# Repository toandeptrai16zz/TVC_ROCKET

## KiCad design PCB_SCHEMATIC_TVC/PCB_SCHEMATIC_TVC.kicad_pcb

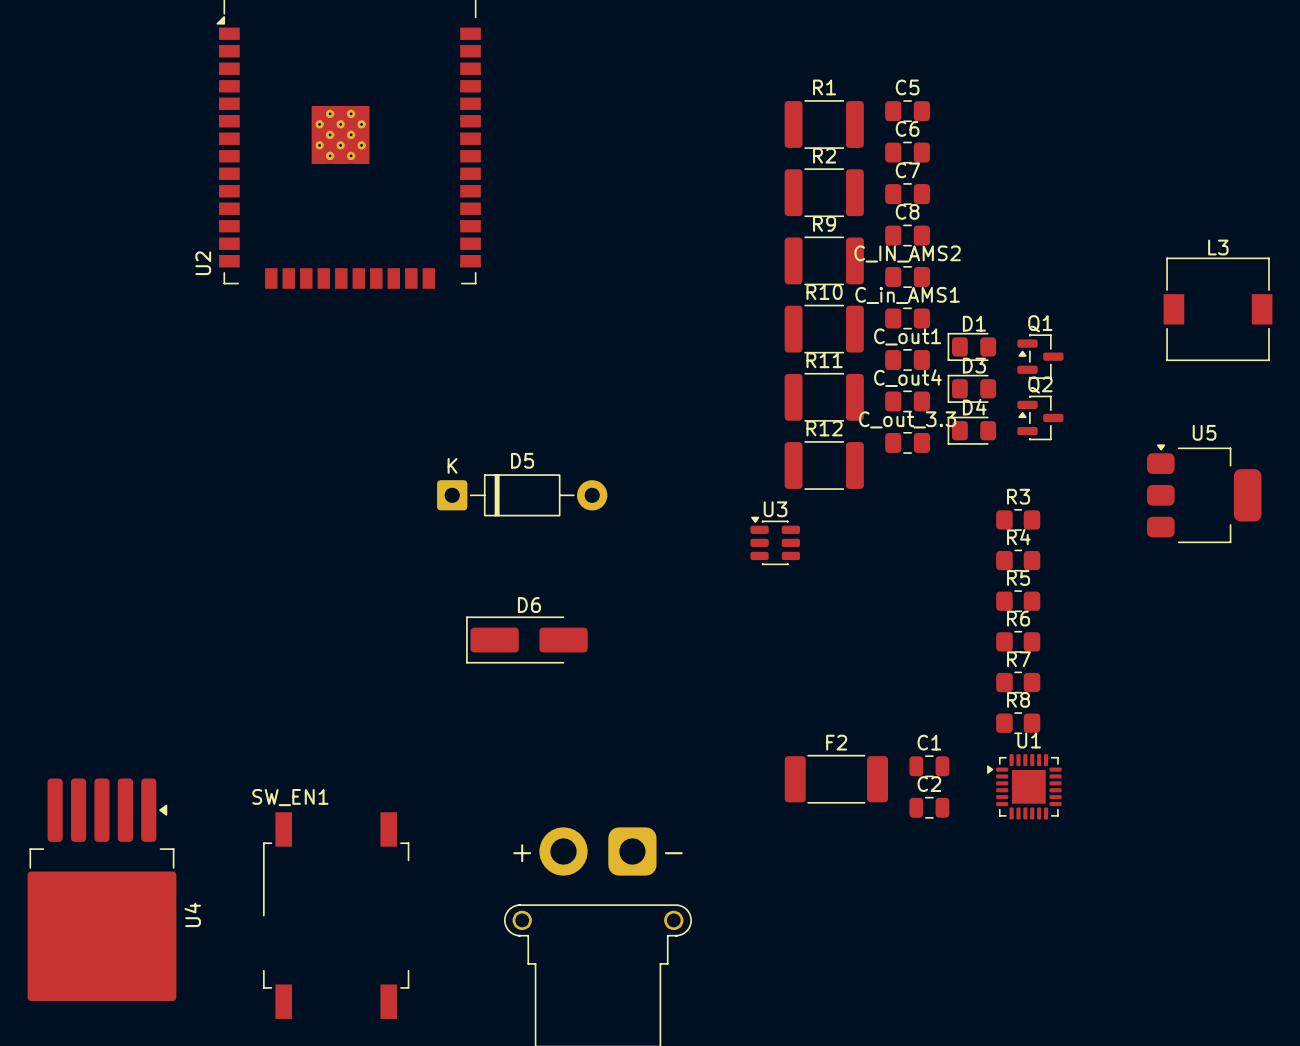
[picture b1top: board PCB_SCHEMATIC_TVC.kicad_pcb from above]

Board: 2 copper layers, 39 parts (0 on the bottom side), 21 nets, no tracks yet.

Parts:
C1, C2: 10uF; C_0805_2012Metric
C5: 4.7uF; C_0805_2012Metric_Pad1.18x1.45mm_HandSolder
C6, C8: 100nF; C_0805_2012Metric_Pad1.18x1.45mm_HandSolder
C7: 10uF; C_0805_2012Metric_Pad1.18x1.45mm_HandSolder
C_IN_AMS2: 1uF; C_0805_2012Metric_Pad1.18x1.45mm_HandSolder
C_in_AMS1: 10uF; C_0805_2012Metric_Pad1.18x1.45mm_HandSolder
C_out1: 220uF; C_0805_2012Metric_Pad1.18x1.45mm_HandSolder
C_out4: 1uF; C_0805_2012Metric_Pad1.18x1.45mm_HandSolder
C_out_3.3: 10uF; C_0805_2012Metric_Pad1.18x1.45mm_HandSolder
D1, D3, D4: LED; LED_0805_2012Metric_Pad1.15x1.40mm_HandSolder
D5: 1N5817; D_DO-41_SOD81_P10.16mm_Horizontal
D6: SS34; D_SMA_Handsoldering
F2: Fuse; Fuse_2512_6332Metric_Pad1.52x3.35mm_HandSolder
J2: Conn_01x02; AMASS_XT30PW-F_1x02_P2.50mm_Horizontal
L3: 33uH; L_7.3x7.3_H3.5
Q1, Q2: SS8050; SOT-23
R1, R2: 5k1; R_1812_4532Metric_Pad1.30x3.40mm_HandSolder
R3, R7: 1k; R_0805_2012Metric_Pad1.20x1.40mm_HandSolder
R4: 1K; R_0805_2012Metric_Pad1.20x1.40mm_HandSolder
R5: 22k; R_0805_2012Metric_Pad1.20x1.40mm_HandSolder
R6: 47k; R_0805_2012Metric_Pad1.20x1.40mm_HandSolder
R8: 1.5k; R_0805_2012Metric_Pad1.20x1.40mm_HandSolder
R9, R10, R11, R12: 10k; R_1812_4532Metric_Pad1.30x3.40mm_HandSolder
SW_EN1: SW_MEC_5GSH9
U1: CP2102C-Axx-xQFN24; WQFN-24-1EP_4x4mm_P0.5mm_EP2.45x2.45mm
U2: ESP32-WROOM-32
U3: USBLC6-2SC6; SOT-23-6
U4: LM2596S-5; TO-263-5_TabPin3
U5: AMS1117-3.3; SOT-223-3_TabPin2

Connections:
+3.3V: C5.1, C6.1, C7.1, C8.1, C_out4.1, C_out_3.3.2, R3.1, R4.1, R11.2, R12.1, U1.5 (VIO), U1.6 (VDD), U1.7 (VREGIN), U2.2 (VDD), U5.2 (VO)
/5V_BAT: C1.1, C_IN_AMS2.1, C_in_AMS1.1, C_out1.1, D5.1 (K), L3.2, R7.1, U3.5 (VBUS), U4.4 (FB), U5.3 (VI)
/BAT_4S: F2.1, J2.2, R8.1
DTR_CP2102: Q1.2 (E), R10.1, U1.23 (~DTR)
EN: C2.1, Q1.3 (C), R11.1, SW_EN1.3 (B), SW_EN1.4 (B), U2.3 (EN)
GND: C1.2, C2.2, C5.2, C6.2, C7.2, C8.2, C_IN_AMS2.2, C_in_AMS1.2, C_out1.2, C_out4.2, C_out_3.3.1, D1.1 (K), D3.1 (K), D4.1 (K), D6.2 (A), J2.1, R1.2, R2.2, R6.2, SW_EN1.1 (A), SW_EN1.2 (A), U1.2 (GND), U1.25 (GND), U2.1 (GND), U2.15 (GND), U2.38 (GND), U2.39 (GND), U3.2 (GND), U4.3 (GND), U4.5 (~ON/OFF), U5.1 (GND)
IO_0: Q2.3 (C), R12.2, U2.25 (IO0)
unnamed: D1.2 (A), R3.2
unnamed: D3.2 (A), R7.2
unnamed: D4.2 (A), R8.2
unnamed: D6.1 (K), L3.1, U4.2 (OUT)
unnamed: Q1.1 (B), R9.2
unnamed: Q2.1 (B), R10.2
unnamed: R5.2, R6.1, U1.8 (VBUS)
unnamed: R4.2, U1.9 (~RST)
unnamed: F2.2, U4.1 (VIN)
RTS_CP2102: Q2.2 (E), R9.1, U1.19 (~RTS)
RX_CP2102: U1.20 (RXD), U2.35 (TXD0/IO1)
TX_CP2102: U1.21 (TXD), U2.34 (RXD0/IO3)
USB_D+: U1.3 (D+), U3.6 (I/O1)
USB_D-: U1.4 (D-), U3.4 (I/O2)

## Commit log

2026-05-25 Vẽ Schematic esp usb C , flash, power
